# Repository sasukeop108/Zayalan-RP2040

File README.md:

# Zayalan RP2040
A rp2040 board designed by me following the tutorial by kai. I wuld use this in my upcoming projects like my keyboard.

# PCB

# schematic

# BOM

| Field | Data |
| :--- | :--- |
| **BOM Name** | bom-JLCPCB Assembly Order.xlsx |
| **Download Time** | 2026-03-22 21:53:15 |
| **PCB Qty** | 5 |
| **Est. Total Price** | $15.9319 |

### **Matched Parts Table**

| Designator | Comment | Footprint | JLCPCB Part # | Status | Manufacturer | Description | Lib Type | Qty | Total Price |
| :--- | :--- | :--- | :--- | :--- | :--- | :--- | :--- | :--- | :--- |
| C1 | 0.1uF | 0402 | **C1525** | Unconfirmed | Samsung | 100nF 16V X7R | Basic | 55 | $0.0715 |
| C2-C8, C11-C17 | 0.1uF | 0402 | **C1525** | Unconfirmed | Samsung | 100nF 16V X7R | Basic | 55 | $0.0715 |
| C9, C10 | 1uF | 0402 | **C52923** | System | Samsung | 1uF 25V X5R | Basic | 10 | $0.0400 |
| C13, C16 | 15pF | 0402 | **C1548** | System | Fenghua | 15pF 50V C0G | Basic | 10 | $0.0130 |
| C14, C15 | 10uF | 0603 | **C19702** | System | Samsung | 10V 10uF X5R | Basic | 10 | $0.0720 |
| D1 | LED | 01005 | **C2929611** | Unconfirmed | PARALIGHT | Yellow Green SIP-4 | Extended | 0 | $0.0000 |
| J1 | USB_C | Type-C-31 | **C165948** | Customer | Hroparts | 16P Female SMD | Extended | 5 | $0.9060 |
| R1, R2 | 5.1k | 0402 | **C25905** | Unconfirmed | UNI-ROYAL | 5.1kΩ ±1% | Basic | 10 | $0.0080 |
| R3, R4 | 27 | 0402 | **C25100** | Unconfirmed | UNI-ROYAL | 27Ω ±1% | Extended | 22 | $0.0176 |
| R6 | 10K | 0402 | **C25744** | Unconfirmed | UNI-ROYAL | 10kΩ ±1% | Basic | 5 | $0.0040 |
| R5, R7, R12 | 1K | 0402 | **C11702** | Unconfirmed | UNI-ROYAL | 1kΩ ±1% | Basic | 15 | $0.0105 |
| SW1 | SW_Push | 4x3mm | **C398055** | Customer | SHOU HAN | Tactile Switch | Extended | 9 | $0.3258 |
| U1 | RP2040 | QFN-56 | **C2040** | Customer | Raspberry Pi | MCU 133MHz | Extended | 5 | $4.8295 |
| U2 | W25Q128JVS | USON-8 | **C2843335** | Customer | Winbond | 16Mbit NOR Flash | Extended | 5 | $8.3310 |
| Y2 | 12MHz | 3225-4P | **C481407** | System | NDK | Crystal 8pF | Extended | 5 | $1.2315 |
| J4 | Conn_01x03 | 2.54mm | — | **No Match** | — | — | — | — | — |
| U3 | MCP1700x | SOT-89-3 | — | **No Match** | — | — | — | — | — |
# Note
You might tell me to just get 2 pcbs assembled i too tried but it is not possible due to some unfortunate reasons the 2 peice button is not woking for me

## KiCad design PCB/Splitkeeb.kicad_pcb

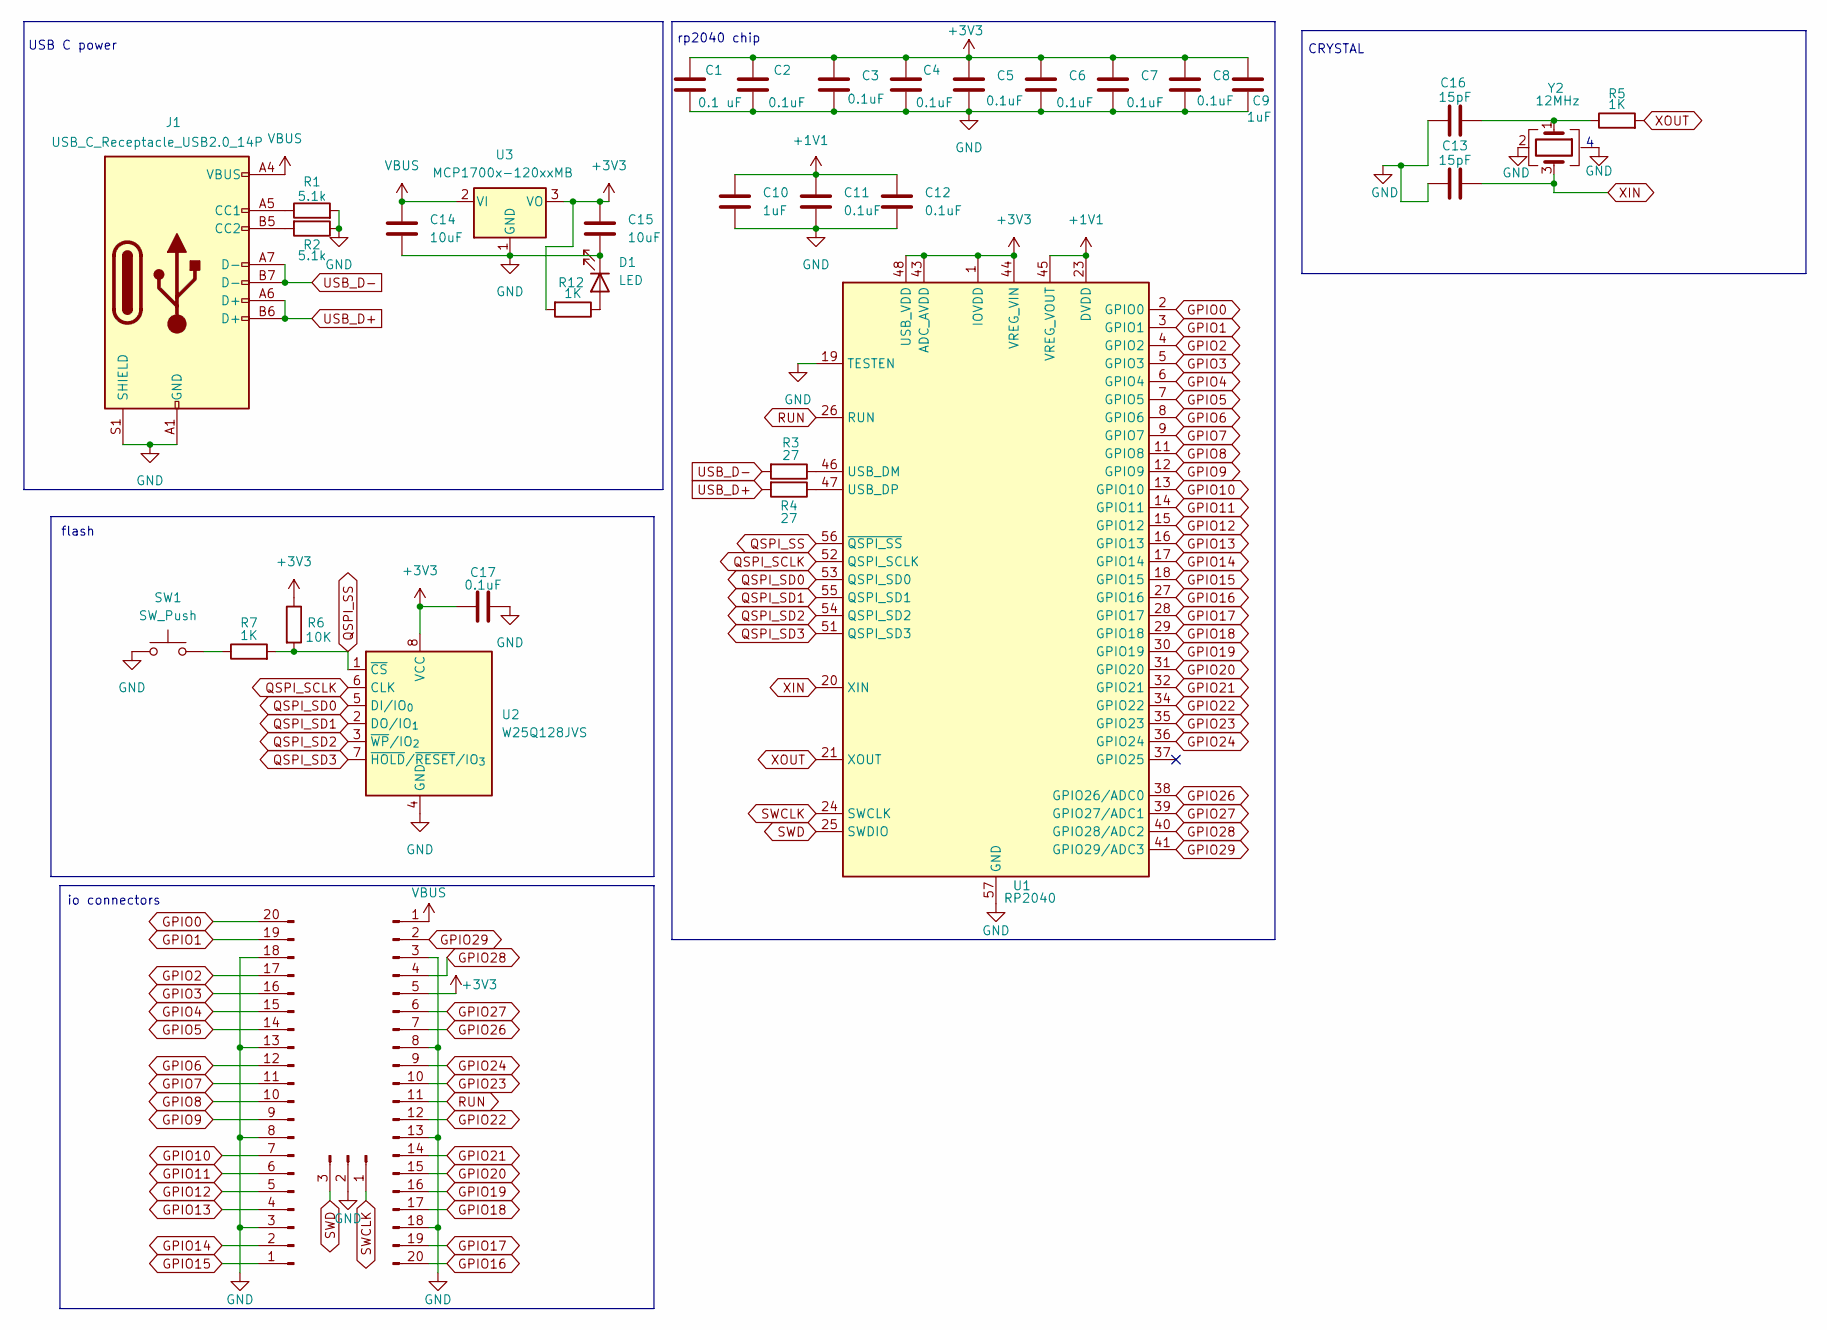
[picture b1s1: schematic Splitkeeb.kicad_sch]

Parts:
C1: 0.1 uF; C_0402_1005Metric
C2, C3, C4, C5, C6, C7, C8, C11, C12, C17: 0.1uF; C_0402_1005Metric
C9, C10: 1uF; C_0402_1005Metric
C13, C16: 15pF; C_0402_1005Metric
C14, C15: 10uF; C_0603_1608Metric
D1: LED; LED_01005_0402Metric
J1: USB_C_Receptacle_USB2.0_14P; USB_C_Receptacle_HRO_TYPE-C-31-M-12
J2: PinHeader_1x20_P2.54mm_Vertical
J3: Conn_01x20_Pin; PinHeader_1x20_P2.54mm_Vertical
J4: Conn_01x03_Pin; PinHeader_1x03_P2.54mm_Vertical
R1, R2: 5.1k; R_0402_1005Metric
R3, R4: 27; R_0402_1005Metric
R5, R7, R12: 1K; R_0402_1005Metric
R6: 10K; R_0402_1005Metric
SW1: SW_Push; SW_Push_SPST_NO_Alps_SKRK
U1: RP2040; QFN-56-1EP_7x7mm_P0.4mm_EP3.2x3.2mm
U2: W25Q128JVS; Winbond_USON-8-1EP_3x2mm_P0.5mm_EP0.2x1.6mm
U3: MCP1700x-120xxMB; SOT-89-3
Y2: 12MHz; Crystal_SMD_3225-4Pin_3.2x2.5mm

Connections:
+1V1: C10.1, C11.1, C12.1, U1.23 (DVDD), U1.45 (VREG_VOUT), U1.50 (DVDD)
+3V3: C1.1, C2.1, C3.1, C4.1, C5.1, C6.1, C7.1, C8.1, C9.1, C15.1, C17.2, J3.5, R6.1, R12.2, U1.1 (IOVDD), U1.10 (IOVDD), U1.22 (IOVDD), U1.33 (IOVDD), U1.42 (IOVDD), U1.43 (ADC_AVDD), U1.44 (VREG_VIN), U1.48 (USB_VDD), U1.49 (IOVDD), U2.8 (VCC), U3.3 (VO)
GND: C1.2, C2.2, C3.2, C4.2, C5.2, C6.2, C7.2, C8.2, C9.2, C10.2, C11.2, C12.2, C13.2, C14.2, C15.2, C16.2, C17.1, D1.1 (K), J1.A1 (GND), J1.A12 (GND), J1.B1 (GND), J1.B12 (GND), J1.S1 (SHIELD), J2.3, J2.8, J2.13, J2.18, J3.3, J3.8, J3.13, J3.18, J4.2, R1.2, R2.1, SW1.1, U1.19 (TESTEN), U1.57 (GND), U2.4 (GND), U3.1 (GND), Y2. (4), Y2.2 (G), Y2.4 (G)
GPIO0: J2.20, U1.2 (GPIO0)
GPIO1: J2.19, U1.3 (GPIO1)
GPIO2: J2.17, U1.4 (GPIO2)
GPIO3: J2.16, U1.5 (GPIO3)
GPIO4: J2.15, U1.6 (GPIO4)
GPIO5: J2.14, U1.7 (GPIO5)
GPIO6: J2.12, U1.8 (GPIO6)
GPIO7: J2.11, U1.9 (GPIO7)
GPIO8: J2.10, U1.11 (GPIO8)
GPIO9: J2.9, U1.12 (GPIO9)
GPIO10: J2.7, U1.13 (GPIO10)
GPIO11: J2.6, U1.14 (GPIO11)
GPIO12: J2.5, U1.15 (GPIO12)
GPIO13: J2.4, U1.16 (GPIO13)
GPIO14: J2.2, U1.17 (GPIO14)
GPIO15: J2.1, U1.18 (GPIO15)
GPIO16: J3.20, U1.27 (GPIO16)
GPIO17: J3.19, U1.28 (GPIO17)
GPIO18: J3.17, U1.29 (GPIO18)
GPIO19: J3.16, U1.30 (GPIO19)
GPIO20: J3.15, U1.31 (GPIO20)
GPIO21: J3.14, U1.32 (GPIO21)
GPIO22: J3.12, U1.34 (GPIO22)
GPIO23: J3.10, U1.35 (GPIO23)
GPIO24: J3.9, U1.36 (GPIO24)
GPIO26: J3.7, U1.38 (GPIO26/ADC0)
GPIO27: J3.6, U1.39 (GPIO27/ADC1)
GPIO28: J3.4, U1.40 (GPIO28/ADC2)
GPIO29: J3.2, U1.41 (GPIO29/ADC3)
unnamed: C16.1, R5.1, Y2.1
unnamed: D1.2 (A), R12.1
unnamed: J1.A5 (CC1), R1.1
unnamed: J1.B5 (CC2), R2.2
unnamed: R7.1, SW1.2
unnamed: R3.1, U1.46 (USB_DM)
unnamed: R4.1, U1.47 (USB_DP)
QSPI_SCLK: U1.52 (QSPI_SCLK), U2.6 (CLK)
QSPI_SD0: U1.53 (QSPI_SD0), U2.5 (DI/IO_{0})
QSPI_SD1: U1.55 (QSPI_SD1), U2.2 (DO/IO_{1})
QSPI_SD2: U1.54 (QSPI_SD2), U2.3 (~WP/IO_{2})
QSPI_SD3: U1.51 (QSPI_SD3), U2.7 (~HOLD/~RESET/IO_{3})
QSPI_SS: R6.2, R7.2, U1.56 (~QSPI_SS), U2.1 (~CS)
RUN: J3.11, U1.26 (RUN)
SWCLK: J4.1, U1.24 (SWCLK)
SWD: J4.3, U1.25 (SWDIO)
USB_D+: J1.A6 (D+), J1.B6 (D+), R4.2
USB_D-: J1.A7 (D-), J1.B7 (D-), R3.2
VBUS: C14.1, J1.A4 (VBUS), J1.A9 (VBUS), J1.B4 (VBUS), J1.B9 (VBUS), J3.1, U3.2 (VI)
XIN: C13.1, U1.20 (XIN), Y2.3
XOUT: R5.2, U1.21 (XOUT)

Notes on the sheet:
USB C power
flash
CRYSTAL
rp2040 chip
io connectors

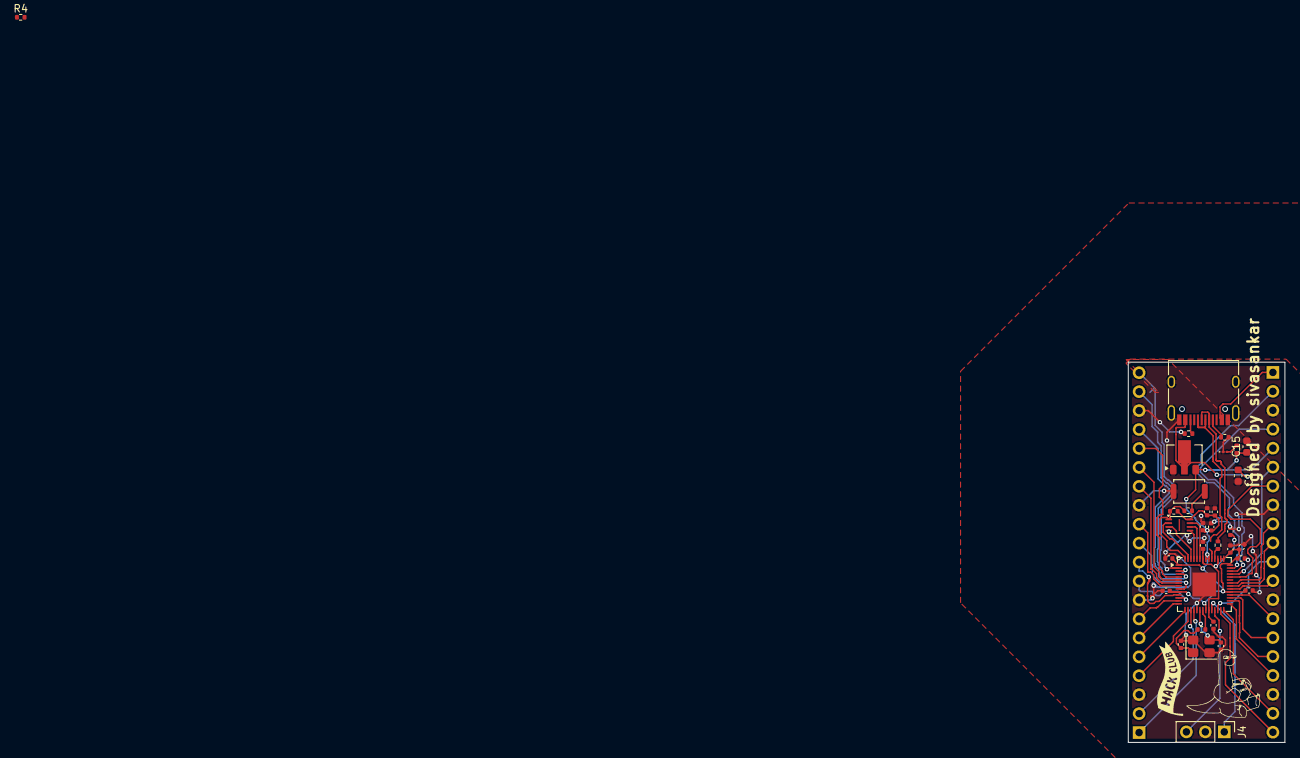
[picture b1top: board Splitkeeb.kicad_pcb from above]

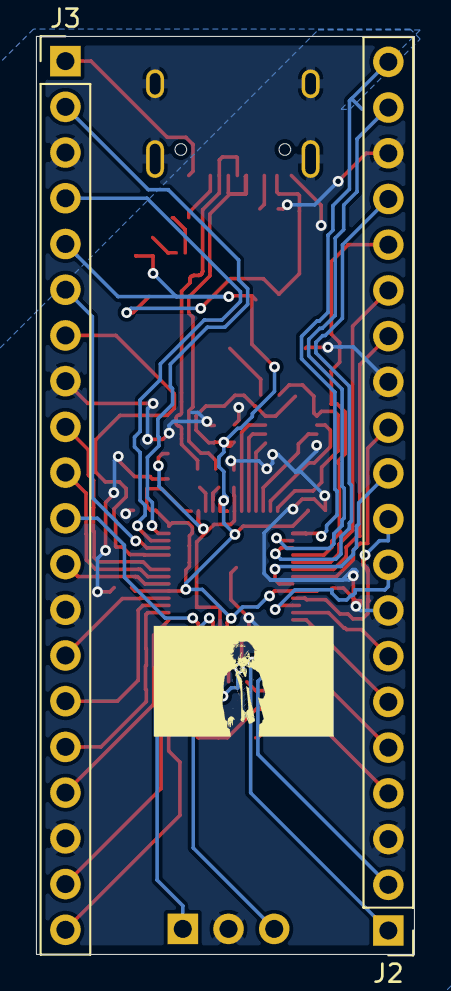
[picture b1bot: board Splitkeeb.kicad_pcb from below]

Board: 2 copper layers, 21.0 x 51.0 mm, 35 parts (2 on the bottom side), 53 nets.

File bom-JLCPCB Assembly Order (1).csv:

JLCPCB BOM Tool - BOM Matching,,,,,,,,,,,,,,,,,
BOM name：bom-JLCPCB Assembly Order.xlsx,,,Download Time：2026-03-22 21:38:30,,,,"* Our matching results are updated in real-time, but stock and prices may change. 
If it's been over 24 hours, please re-match before placing your order.",,,,,,,,,,
PCB Assembled Qty：5,,,Est. Total Price：15.9319,,,,,,,,,,,,,,
Your BOM,,,,,Matched Parts,,,,,,,Order Information,,,,,
Top Designator,Bottom Designator,Comment,Footprint,JLCPCB Part #,Matches,Part # ,Manufacturer,Footprint,Description,Category,Warning,JLCPCB Part #,Product link,Lib Type,Qty,Source,Total Price ($)
C1,,0.1uF,0402,,Unconfirmed,CL05B104KO5NNNC,Samsung Electro-Mechanics,0402,100nF 16V X7R ±10% 0402 Multilayer Ceramic Capacitors MLCC - SMD/SMT ROHS,Multilayer Ceramic Capacitors MLCC - SMD/SMT,1.The comment (CL05B104KO5NNNC) of this part does not match the one (0.1uF) provided in your BOM. Please confirm;,C1525,https://jlcpcb.com/partdetail/1877-CL05B104KO5NNNC/C1525,Basic,55,55 JLCPCB,0.0715
"C11,C12,C17,C2,C3,C4,C5,C6,C7,C8",,0.1uF,0402,,Unconfirmed,CL05B104KO5NNNC,Samsung Electro-Mechanics,0402,100nF 16V X7R ±10% 0402 Multilayer Ceramic Capacitors MLCC - SMD/SMT ROHS,Multilayer Ceramic Capacitors MLCC - SMD/SMT,1.The comment (CL05B104KO5NNNC) of this part does not match the one (0.1uF) provided in your BOM. Please confirm;,C1525,https://jlcpcb.com/partdetail/1877-CL05B104KO5NNNC/C1525,Basic,55,55 JLCPCB,0.0715
"C10,C9",,1uF,0402,,Select by System,CL05A105KA5NQNC,Samsung Electro-Mechanics,0402,1uF 25V X5R ±10% 0402 Multilayer Ceramic Capacitors MLCC - SMD/SMT ROHS,Multilayer Ceramic Capacitors MLCC - SMD/SMT,,C52923,https://jlcpcb.com/partdetail/53938-CL05A105KA5NQNC/C52923,Basic,10,10 JLCPCB,0.04
"C13,C16",,15pF,0402,,Select by System,0402CG150J500NT,FH (Guangdong Fenghua Advanced Tech),0402,15pF 50V C0G ±5% 0402 Multilayer Ceramic Capacitors MLCC - SMD/SMT ROHS,Multilayer Ceramic Capacitors MLCC - SMD/SMT,,C1548,https://jlcpcb.com/partdetail/1900-0402CG150J500NT/C1548,Basic,10,10 JLCPCB,0.013
"C14,C15",,10uF,0603,,Select by System,CL10A106KP8NNNC,Samsung Electro-Mechanics,0603,10V 10uF X5R ±10% 0603 Multilayer Ceramic Capacitors MLCC - SMD/SMT ROHS,Multilayer Ceramic Capacitors MLCC - SMD/SMT,,C19702,https://jlcpcb.com/partdetail/20411-CL10A106KP8NNNC/C19702,Basic,10,10 JLCPCB,0.072
D1,,LED,01005,,Unconfirmed,B-1005G-3V-EP,PARALIGHT,SIP-4-2.5mm,-35℃~+85℃ 10mm Square Lens 2.2V 20mA 3mcd 568nm 570nm 75mW Discrete Diode Yellow Green SIP-4-2.5mm LED Indication - Discrete ROHS,LED Indication - Discrete,1.The comment (B-1005G-3V-EP) of this part does not match the one (LED) provided in your BOM. Please confirm;,C2929611,https://jlcpcb.com/partdetail/PARALIGHT-B_1005G_3VEP/C2929611,Extended,0,0 JLCPCB,0
J1,,USB_C_Receptacle_USB2.0_14P,USB_C_Receptacle_HRO_TYPE-C-31-M-12,,Select by Customer,TYPE-C-31-M-12,Korean Hroparts Elec,SMD,"-30℃~+80℃ 1 10,000 cycles 16P 20V 5A 7.35mm Female Surface Mount, Right Angle Type-C SMD USB Connectors ROHS",USB Connectors,,C165948,https://jlcpcb.com/partdetail/Korean_HropartsElec-TYPE_C_31_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,Extended,5,5 JLCPCB,0.906
"R1,R2",,5.1k,0402,,Unconfirmed,0402WGF5101TCE,UNI-ROYAL(Uniroyal Elec),0402,-55℃~+155℃ 5.1kΩ 50V 62.5mW Thick Film Resistor ±1% ±100ppm/℃ 0402 Chip Resistor - Surface Mount ROHS,Chip Resistor - Surface Mount,1.The comment (0402WGF5101TCE) of this part does not match the one (5.1k) provided in your BOM. Please confirm;,C25905,https://jlcpcb.com/partdetail/26648-0402WGF5101TCE/C25905,Basic,10,10 JLCPCB,0.008
"R3,R4",,27,0402,,Unconfirmed,0402WGF270JTCE,UNI-ROYAL(Uniroyal Elec),0402,-55℃~+155℃ 27Ω 50V 62.5mW Thick Film Resistor ±1% ±100ppm/℃ 0402 Chip Resistor - Surface Mount ROHS,Chip Resistor - Surface Mount,1.The comment (0402WGF270JTCE) of this part does not match the one (27) provided in your BOM. Please confirm;,C25100,https://jlcpcb.com/partdetail/25843-0402WGF270JTCE/C25100,Extended,22,22 JLCPCB,0.0176
R6,,10K,0402,,Unconfirmed,0402WGF1002TCE,UNI-ROYAL(Uniroyal Elec),0402,-55℃~+155℃ 10kΩ 50V 62.5mW Thick Film Resistor ±1% ±100ppm/℃ 0402 Chip Resistor - Surface Mount ROHS,Chip Resistor - Surface Mount,1.The comment (0402WGF1002TCE) of this part does not match the one (10K) provided in your BOM. Please confirm;,C25744,https://jlcpcb.com/partdetail/26487-0402WGF1002TCE/C25744,Basic,5,5 JLCPCB,0.004
"R12,R5,R7",,1K,0402,,Unconfirmed,0402WGF1001TCE,UNI-ROYAL(Uniroyal Elec),0402,-55℃~+155℃ 1kΩ 50V 62.5mW Thick Film Resistor ±1% ±100ppm/℃ 0402 Chip Resistor - Surface Mount ROHS,Chip Resistor - Surface Mount,1.The comment (0402WGF1001TCE) of this part does not match the one (1K) provided in your BOM. Please confirm;,C11702,https://jlcpcb.com/partdetail/12256-0402WGF1001TCE/C11702,Basic,15,15 JLCPCB,0.0105
SW1,,SW_Push,SW_Push_SPST_NO_Alps_SKRK,,Select by Customer,TS342A2P,SHOU HAN,"SMD,4x3mm","-20℃~+70℃ 12V 2.5N 2mm 3mm 4mm 50,000 cycles 50mA Black No Round Button SMD(SMT) Tab SPST Surface Mount,Vertical Without Bracket SMD,4x3mm Tactile Switches ROHS",Tactile Switches,,C398055,https://jlcpcb.com/partdetail/SHOUHAN-TS342A2P/C398055,Extended,9,9 JLCPCB,0.3258
U1,,RP2040,QFN-56-1EP_7x7mm_P0.4mm_EP3.2x3.2mm,,Select by Customer,RP2040,Raspberry Pi,LQFN-56(7x7),12bit 133MHz 30 LQFN-56(7x7) Microcontrollers (MCU/MPU/SOC) ROHS,Microcontrollers (MCU/MPU/SOC),,C2040,https://jlcpcb.com/partdetail/RaspberryPi-RP2040/C2040,Extended,5,5 JLCPCB,4.8295
U2,,W25Q128JVS,Winbond_USON-8-1EP_3x2mm_P0.5mm_EP0.2x1.6mm,,Select by Customer,W25Q16JVUXIQ,Winbond Elec,USON-8-EP(2x3),"-40℃~+85℃ 100,000 cycles 10uA 133MHz 16Mbit 2.7V~3.6V 20 Years 3ms SPI USON-8-EP(2x3) NOR FLASH ROHS",NOR FLASH,1.The comment (W25Q16JVUXIQ) of this part does not match the one (W25Q128JVS) provided in your BOM. Please confirm;,C2843335,https://jlcpcb.com/partdetail/WinbondElec-W25Q16JVUXIQ/C2843335,Extended,5,5 JLCPCB,8.331
Y2,,12MHz,Crystal_SMD_3225-4Pin_3.2x2.5mm,,Select by System,NX3225GA-12MHZ-STD-CRG-2,NDK,SMD3225-4P,-40℃~+85℃ 100Ω 12MHz 8pF ±20ppm ±30ppm SMD3225-4P Crystals ROHS,Crystals,,C481407,https://jlcpcb.com/partdetail/NDK-NX3225GA_12MHZ_STD_CRG2/C481407,Extended,5,5 JLCPCB,1.2315
J4,,Conn_01x03_Pin,PinHeader_1x03_P2.54mm_Vertical,,No matches,No Part Selected,,,,,,,,,,,
U3,,MCP1700x-120xxMB,SOT-89-3,,No matches,No Part Selected,,,,,,,,,,,

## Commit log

2026-03-22 Create Production
2026-03-22 Create PCB
2026-03-22 Create D
2026-03-22 Create a
